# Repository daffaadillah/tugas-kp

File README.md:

# Penugasan Kerja Praktik PT. Infoglobal Teknologi Semesta

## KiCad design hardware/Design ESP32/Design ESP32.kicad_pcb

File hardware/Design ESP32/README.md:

# Design ESP32
Proyek Design ESP32 merupakan pembuatan ESP32 dari awal, mulai dari penentuan komponen pembentuk, perancangan komponen, hingga pembuatan design PCB. Tujuan proyek ini adalah membangun sistem ESP32 yang simpel sebagai media pembelajaran.
## Komponen Pembentuk
1. ESP32 S3 WROOM1
2. Regulator LDO 3,3V **AMS1117**
3. Kapasitor bypass (**10µF, 100nF**)  
4. Resistor (**R1, R2, R3, dan R4**)
5. UCB C Receptacle
6. Pin Header 01 × 08
7. S1 (**EN**) dan S2 (**BOOT**)
## Prinsip Kerja
### 1. Power manajemen
-  USB C, menyuplai tegangan 5V.  
-  AMS1117, menurunkan tegangan dari 5V ke 3V. Tegangan 3V yang kemudaian menyuplai ESP32 dan komponen pasif.
### 2. EN dan BOOT
-  EN, untuk mereset board.  
-  BOOT, untuk masuk ke mode pemrograman atau flash mode.
### 3. Resistor dan Kapasitor
-  Digunakan untuk filter tegangan, debouncing tombol, dan stabilisasi startup ESP32.
### 4. USB Data D+, D-
-  Memungkinkan penggunaan USB-TTL eksternal untuk pemrograman via TX/RX.
### 5. Header pin
-  Digunakan sebagai pin I/O eksternal. Bisa dijadikan input, output, PWM, SPI, I2C, UART, dll.

## Cuplikan Schematic

## Cuplikan LayOut PCB

## Cuplikan 3D View

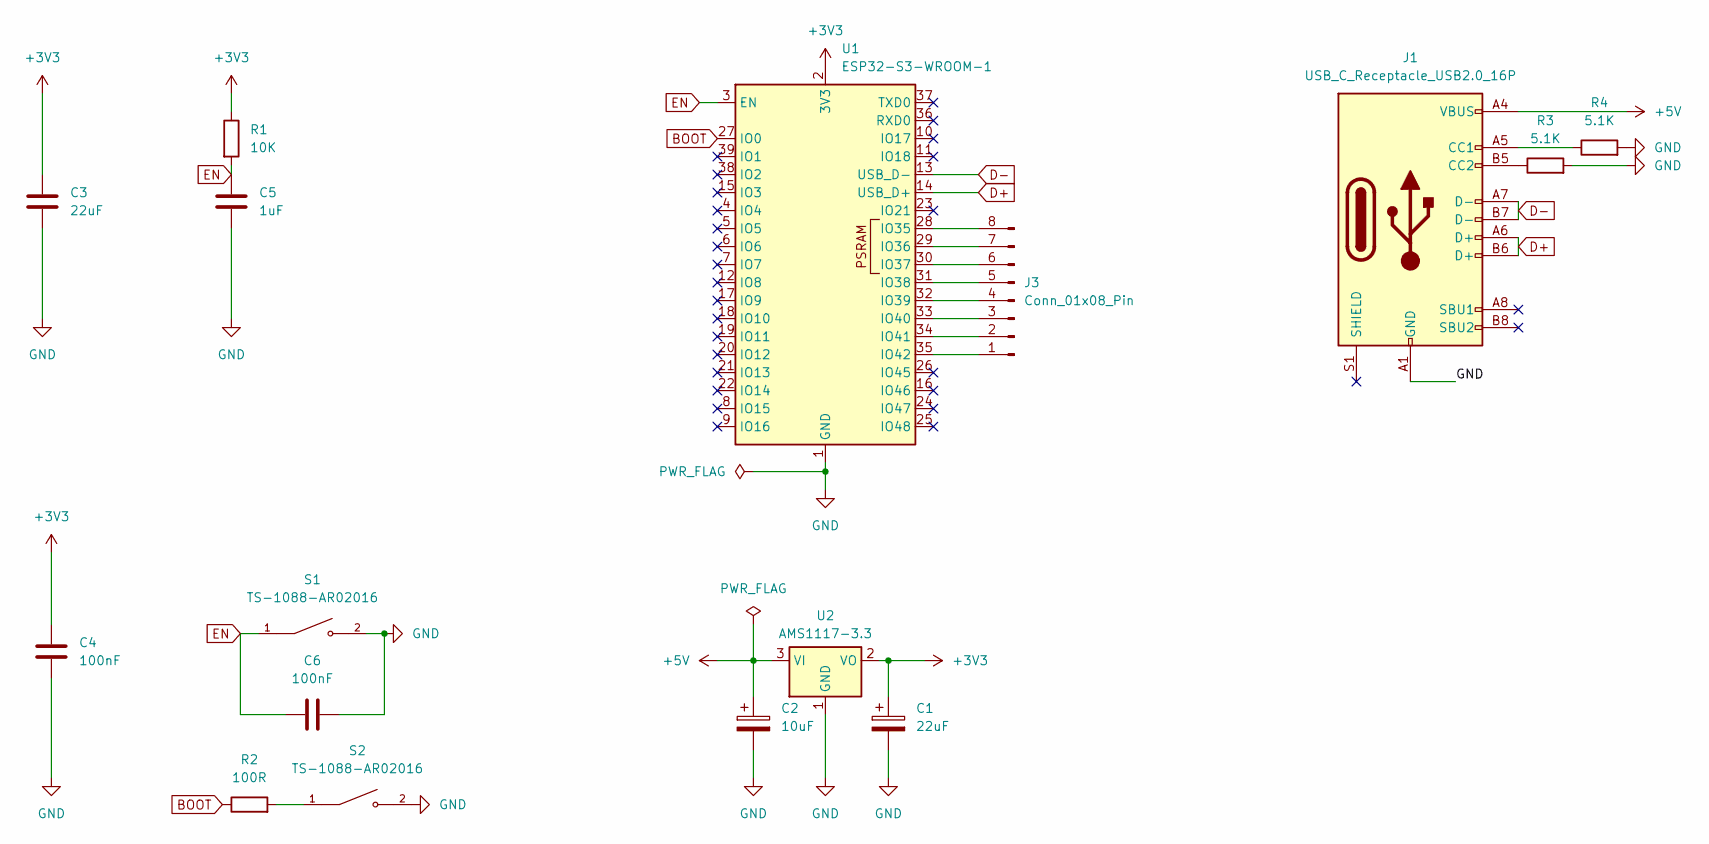
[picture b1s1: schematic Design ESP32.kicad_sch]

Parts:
C1: 22uF; CP_EIA-2012-15_AVX-P
C2: 10uF; CP_EIA-1608-10_AVX-L
C3: 22uF; C_0603_1608Metric
C4: 100nF; C_0603_1608Metric
C5: 1uF; R_0805_2012Metric
C6: 100nF; C_0805_2012Metric
J1: USB_C_Receptacle_USB2.0_16P; USB_C_Receptacle_GCT_USB4105-xx-A_16P_TopMnt_Horizontal
J3: Conn_01x08_Pin; PinHeader_1x08_P1.00mm_Vertical
R1: 10K; C_0805_2012Metric
R2: 100R; R_0805_2012Metric
R3, R4: 5.1K; R_0805_2012Metric
S1, S2: TS-1088-AR02016; SW_TS-1088-AR02016; PARTREV N/A
U1: ESP32-S3-WROOM-1
U2: AMS1117-3.3; SOT-223-3_TabPin2

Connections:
+3V3: C1.1, C3.1, C4.1, R1.1, U1.2 (3V3), U2.2 (VO)
+5V: C2.1, J1.A4 (VBUS), J1.A9 (VBUS), J1.B4 (VBUS), J1.B9 (VBUS), U2.3 (VI)
BOOT: R2.1, U1.27 (IO0)
D+: J1.A6 (D+), J1.B6 (D+), U1.14 (USB_D+)
D-: J1.A7 (D-), J1.B7 (D-), U1.13 (USB_D-)
EN: C5.1, C6.1, R1.2, S1.1, U1.3 (EN)
GND: C1.2, C2.2, C3.2, C4.2, C5.2, C6.2, J1.A1 (GND), J1.A12 (GND), J1.B1 (GND), J1.B12 (GND), R3.2, R4.2, S1.2, S2.2, U1.1 (GND), U1.40 (GND), U1.41 (GND), U2.1 (GND)
unnamed: J1.A5 (CC1), R4.1
unnamed: J1.B5 (CC2), R3.1
unnamed: J3.1, U1.35 (IO42)
unnamed: J3.2, U1.34 (IO41)
unnamed: J3.3, U1.33 (IO40)
unnamed: J3.4, U1.32 (IO39)
unnamed: J3.5, U1.31 (IO38)
unnamed: J3.6, U1.30 (IO37)
unnamed: J3.7, U1.29 (IO36)
unnamed: J3.8, U1.28 (IO35)
unnamed: R2.2, S2.1

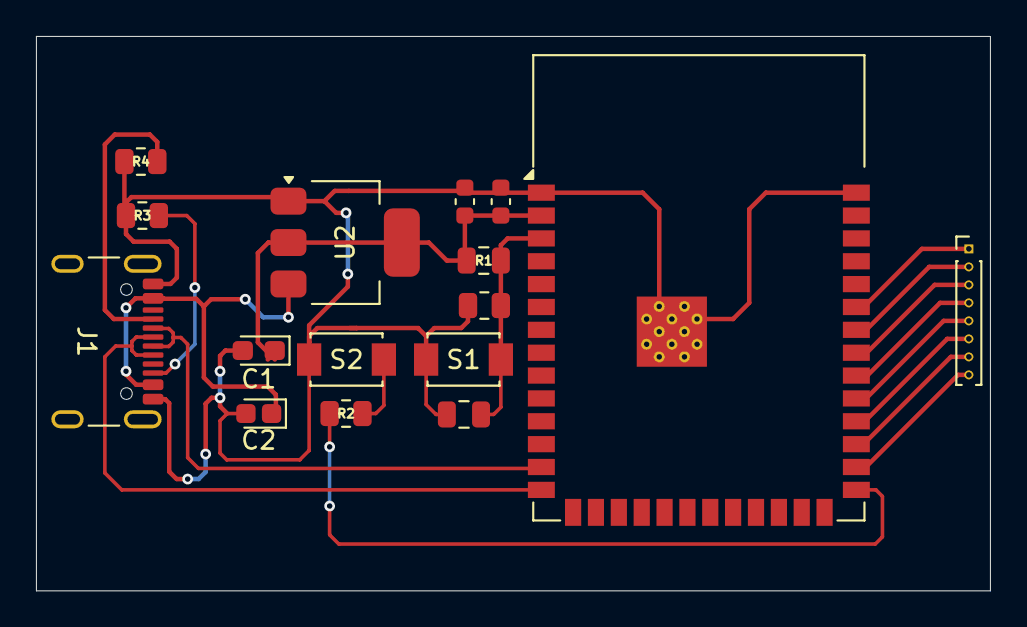
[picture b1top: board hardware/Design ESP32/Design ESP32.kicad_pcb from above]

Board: 2 copper layers, 53.0 x 30.8 mm, 16 parts (0 on the bottom side), 18 nets.

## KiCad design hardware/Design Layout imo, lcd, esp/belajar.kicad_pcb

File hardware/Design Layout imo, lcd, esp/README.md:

# ESP32 motion display module
Proyek ESP32 motion display module merupakan custom PCB untuk ESP32 yang diintegrasikan dengan sensor imo **MPU6050** dan LCD TFT **ILI9341**. Tujuannya yakni untuk dapat menampilkan nilai sudut kemiringan secara real-time dengan display.
## Komponen yang digunakan
-**ESP32 DEVKITV1**  : Mikrokontroler.  
-**MPU6050**         : Sensor accelerometer dan gyroscope 6-axis.  
-**ILI9341**         : Display.  
## Cuplikan Schematic

## kode Arduino IDE
```cpp  
#include <Wire.h>
#include <Adafruit_GFX.h>
#include <Adafruit_ILI9341.h>
#include <MPU6050.h>

// Pin konfigurasi untuk LCD TFT
#define TFT_CS     5
#define TFT_DC     2
#define TFT_RST    4

// Inisialisasi LCD TFT
Adafruit_ILI9341 tft = Adafruit_ILI9341(TFT_CS, TFT_DC, TFT_RST);

// Inisialisasi objek MPU6050
MPU6050 mpu;

void setup() {
  Serial.begin(115200);

  // Inisialisasi I2C MPU6050
  Wire.begin(21, 22); // SDA, SCL
  mpu.initialize();

  if (mpu.testConnection()) {
    Serial.println("MPU6050 connect");
  } else {
    Serial.println("Gagal connect ke MPU6050");
    while (1); // Berhenti
  }

  // Inisialisasi TFT
  tft.begin();
  tft.setRotation(1); // orientasi landscape
  tft.fillScreen(ILI9341_BLACK);
  tft.setTextSize(2);
  tft.setTextColor(ILI9341_WHITE);
}

void loop() {
  int16_t ax, ay, az;
  mpu.getAcceleration(&ax, &ay, &az);

  // menampilkan di serial monitor
  Serial.print("AX: "); Serial.print(ax);
  Serial.print(" AY: "); Serial.print(ay);
  Serial.print(" AZ: "); Serial.println(az);

  // membersihkan dan tampilkan di layar
  tft.fillScreen(ILI9341_BLACK);
  tft.setCursor(10, 20);
  tft.print("Accel X: "); tft.println(ax);

  tft.setCursor(10, 50);
  tft.print("Accel Y: "); tft.println(ay);

  tft.setCursor(10, 80);
  tft.print("Accel Z: "); tft.println(az);

  delay(500);
}
```
## Prinsip kerja
Prinsip kerja alat ini dimulai dari MPU6050 yang berfungsi sebagai sensor percepatan tiga sumbu (X, Y, Z). Sensor ini mendeteksi gerakan atau perubahan posisi, lalu mengirimkan data percepatan tersebut ke ESP32 melalui komunikasi I2C. ESP32 berperan sebagai pusat kontrol yang menerima, mengolah, dan menerjemahkan data percepatan dari sensor. Setelah data terbaca dan diproses, ESP32 mengirimkan hasilnya ke layar TFT LCD melalui komunikasi SPI. Tampilan pada layar diperbarui secara berkala untuk menunjukkan nilai percepatan terbaru dari ketiga sumbu. Dengan demikian, alat tersebut dapat digunakan untuk memantau gerakan atau orientasi secara real-time, yang divisualisasikan langsung melalui display yang mewakili nilai percepatan sumbu X, Y, dan Z.
## Cuplikan hasil custom PCB

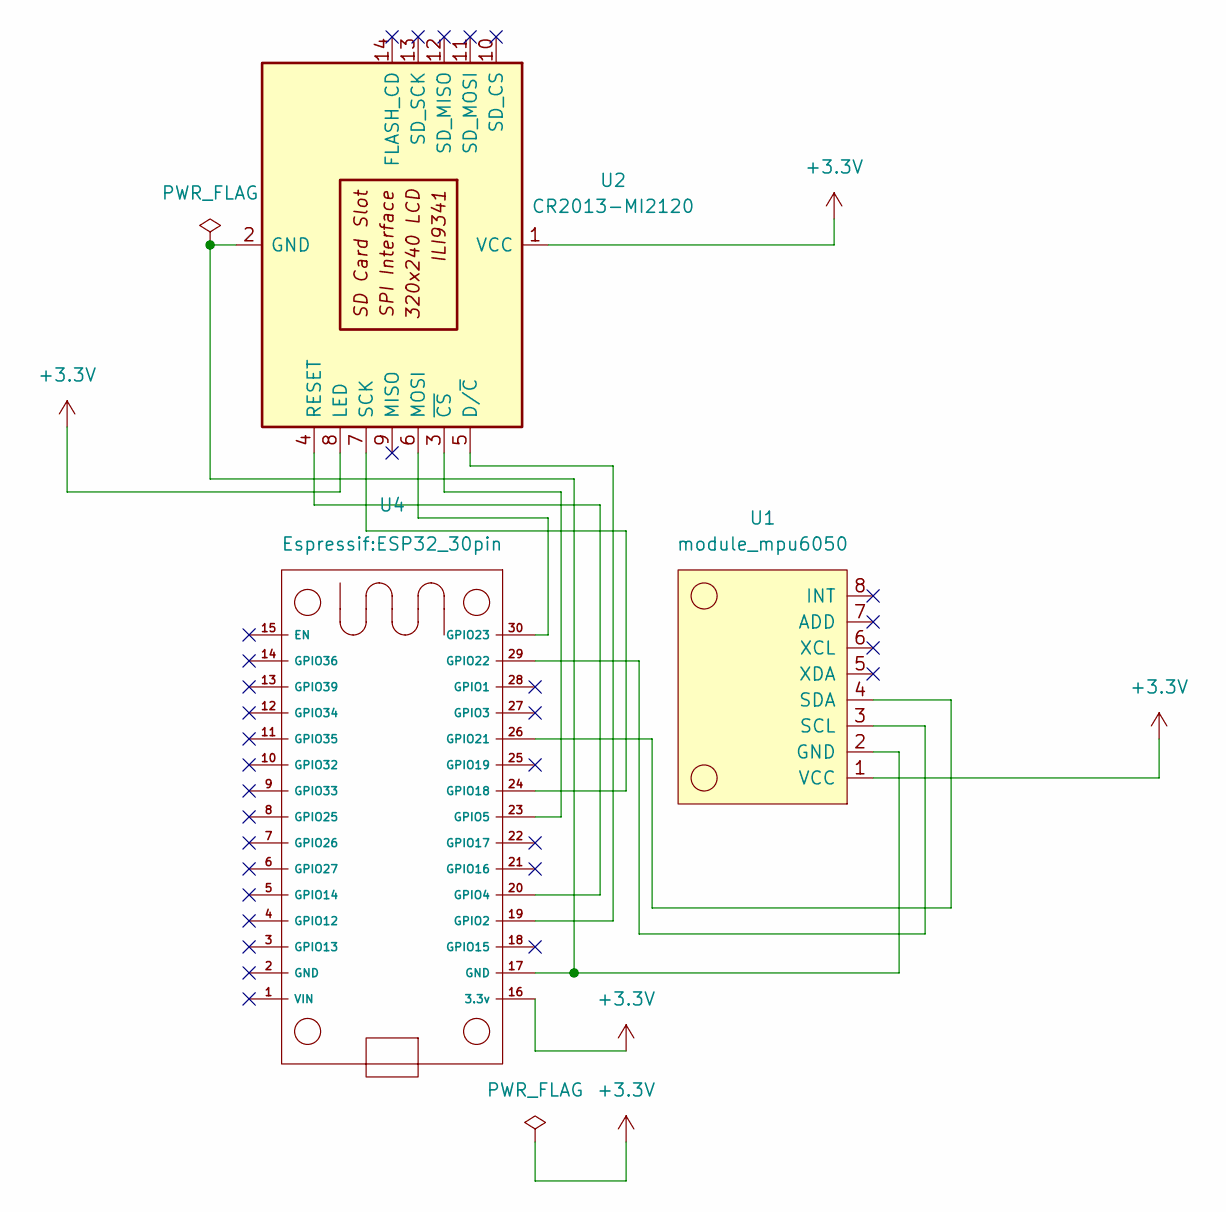
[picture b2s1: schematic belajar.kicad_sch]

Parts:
U1: module_mpu6050
U2: CR2013-MI2120
U4: ESP32_30pin

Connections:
+3.3V: U1.1 (VCC), U2.1 (VCC), U2.8 (LED), U4.16 (3.3v)
unnamed: U1.2 (GND), U2.2 (GND), U4.17 (GND)
unnamed: U1.3 (SCL), U4.29 (GPIO22)
unnamed: U1.4 (SDA), U4.26 (GPIO21)
unnamed: U2.5 (D/~C), U4.19 (GPIO2)
unnamed: U2.6 (MOSI), U4.30 (GPIO23)
unnamed: U2.4 (RESET), U4.20 (GPIO4)
unnamed: U2.7 (SCK), U4.24 (GPIO18)
unnamed: U2.3 (~CS), U4.23 (GPIO5)

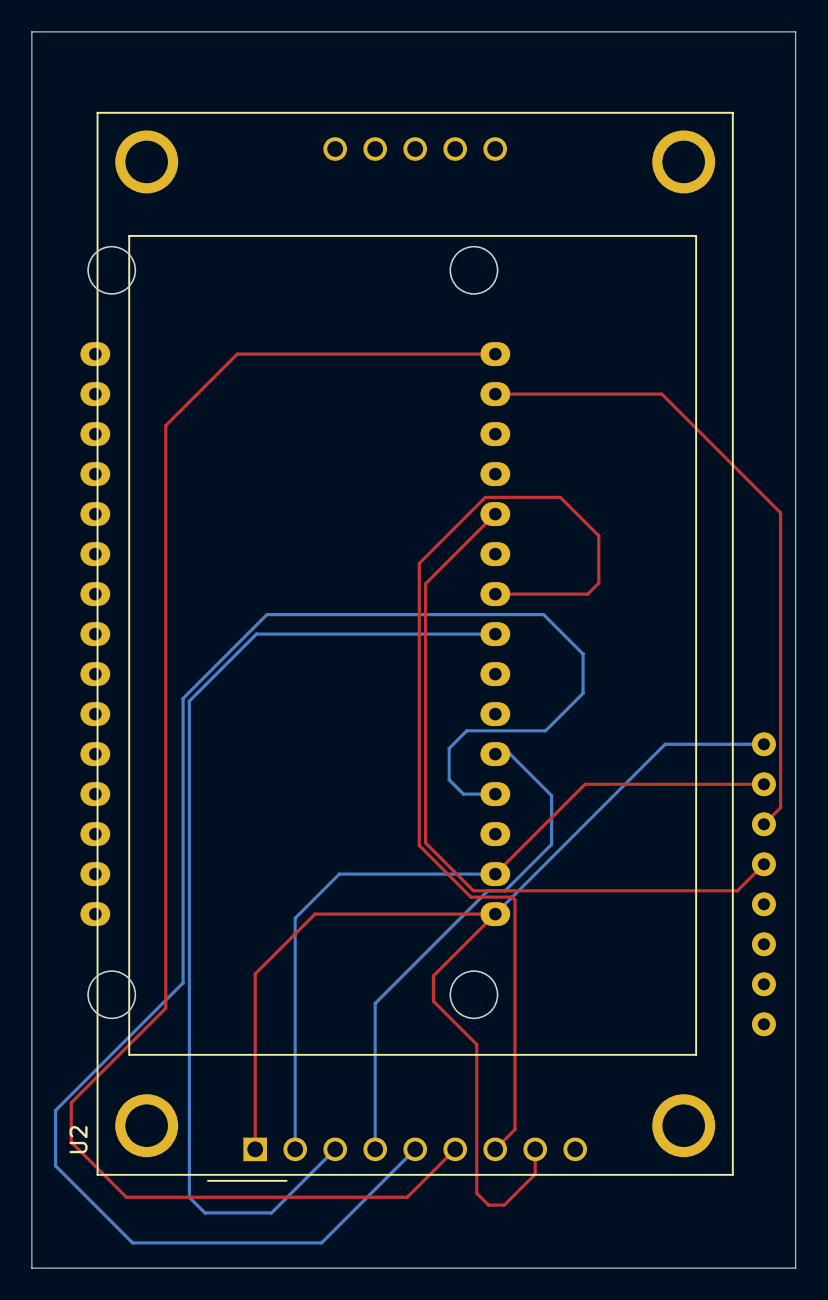
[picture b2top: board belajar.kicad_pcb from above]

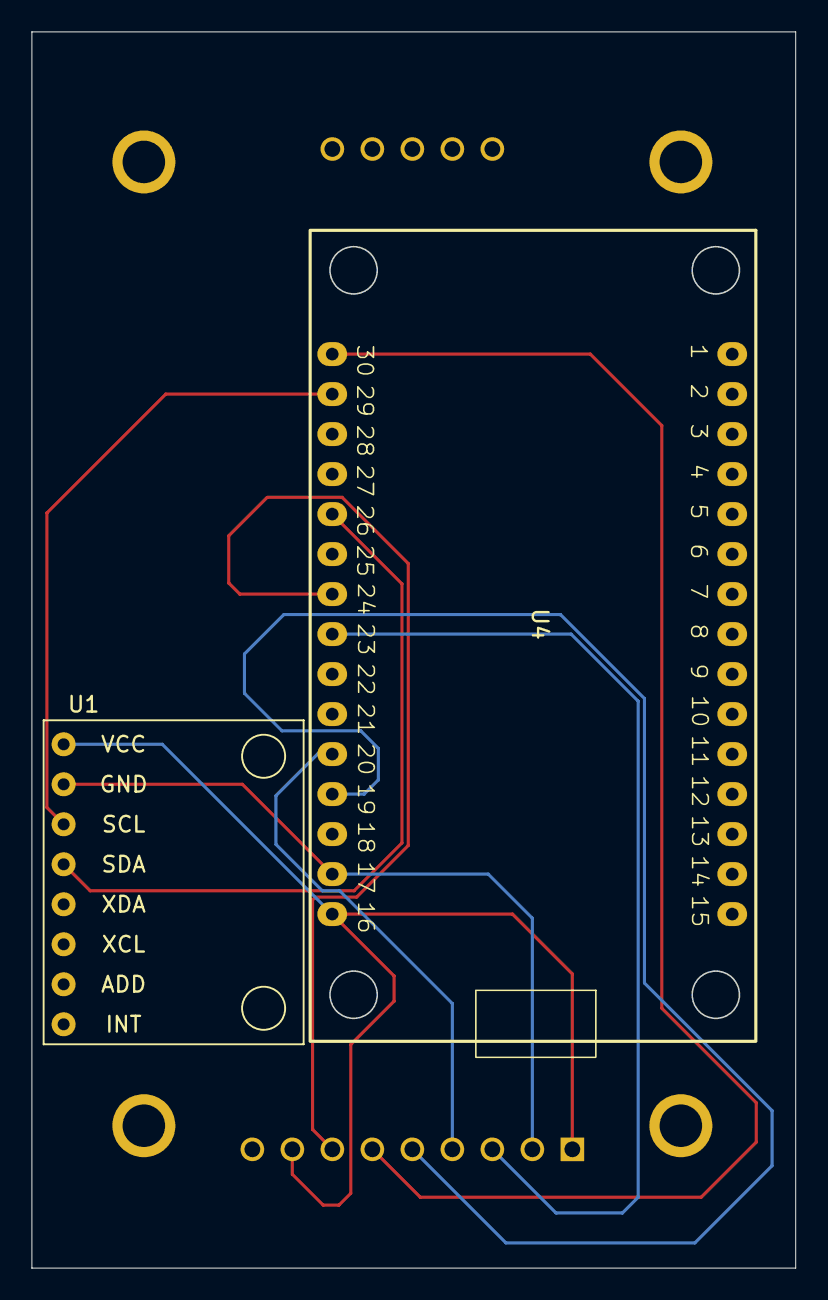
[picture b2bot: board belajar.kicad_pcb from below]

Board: 2 copper layers, 48.5 x 78.5 mm, 3 parts (2 on the bottom side), 9 nets.

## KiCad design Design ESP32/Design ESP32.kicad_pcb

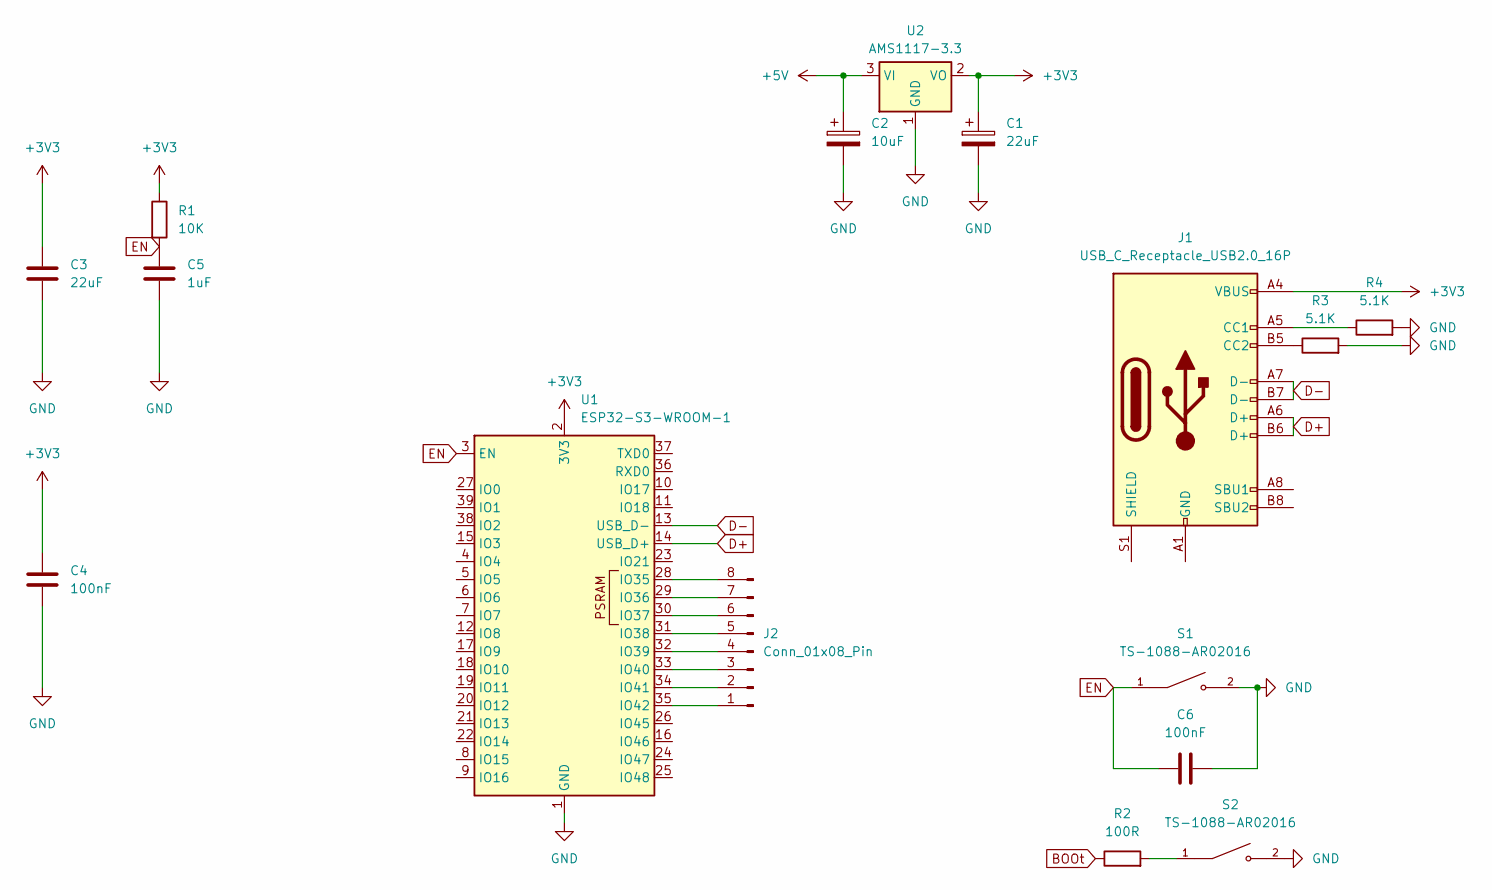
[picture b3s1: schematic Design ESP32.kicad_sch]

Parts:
C1, C3: 22uF; C_0805_2012Metric
C2: 10uF; C_0805_2012Metric
C4, C6: 100nF; C_0805_2012Metric
C5: 1uF; R_0805_2012Metric
J1: USB_C_Receptacle_USB2.0_16P; USB_C_Receptacle_GCT_USB4105-xx-A_16P_TopMnt_Horizontal
J2: Conn_01x08_Pin; PinHeader_1x08_P1.00mm_Vertical
R1: 10K; C_0805_2012Metric
R2: 100R; R_0805_2012Metric
R3, R4: 5.1K; R_0805_2012Metric
S1, S2: TS-1088-AR02016; SW_TS-1088-AR02016; PARTREV N/A
U1: ESP32-S3-WROOM-1
U2: AMS1117-3.3; SOT-223-3_TabPin2

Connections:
+3V3: C1.1, C3.1, C4.1, J1.A4 (VBUS), J1.A9 (VBUS), J1.B4 (VBUS), J1.B9 (VBUS), R1.1, U1.2 (3V3), U2.2 (VO)
+5V: C2.1, U2.3 (VI)
BOOt: R2.1
D+: J1.A6 (D+), J1.B6 (D+), U1.14 (USB_D+)
D-: J1.A7 (D-), J1.B7 (D-), U1.13 (USB_D-)
EN: C5.1, C6.1, R1.2, S1.1, U1.3 (EN)
GND: C1.2, C2.2, C3.2, C4.2, C5.2, C6.2, R3.2, R4.2, S1.2, S2.2, U1.1 (GND), U1.40 (GND), U1.41 (GND), U2.1 (GND)
unnamed: J1.A5 (CC1), R4.1
unnamed: J1.B5 (CC2), R3.1
unnamed: J1.A1 (GND), J1.A12 (GND), J1.B1 (GND), J1.B12 (GND)
unnamed: J2.1, U1.35 (IO42)
unnamed: J2.2, U1.34 (IO41)
unnamed: J2.3, U1.33 (IO40)
unnamed: J2.4, U1.32 (IO39)
unnamed: J2.5, U1.31 (IO38)
unnamed: J2.6, U1.30 (IO37)
unnamed: J2.7, U1.29 (IO36)
unnamed: J2.8, U1.28 (IO35)
unnamed: R2.2, S2.1

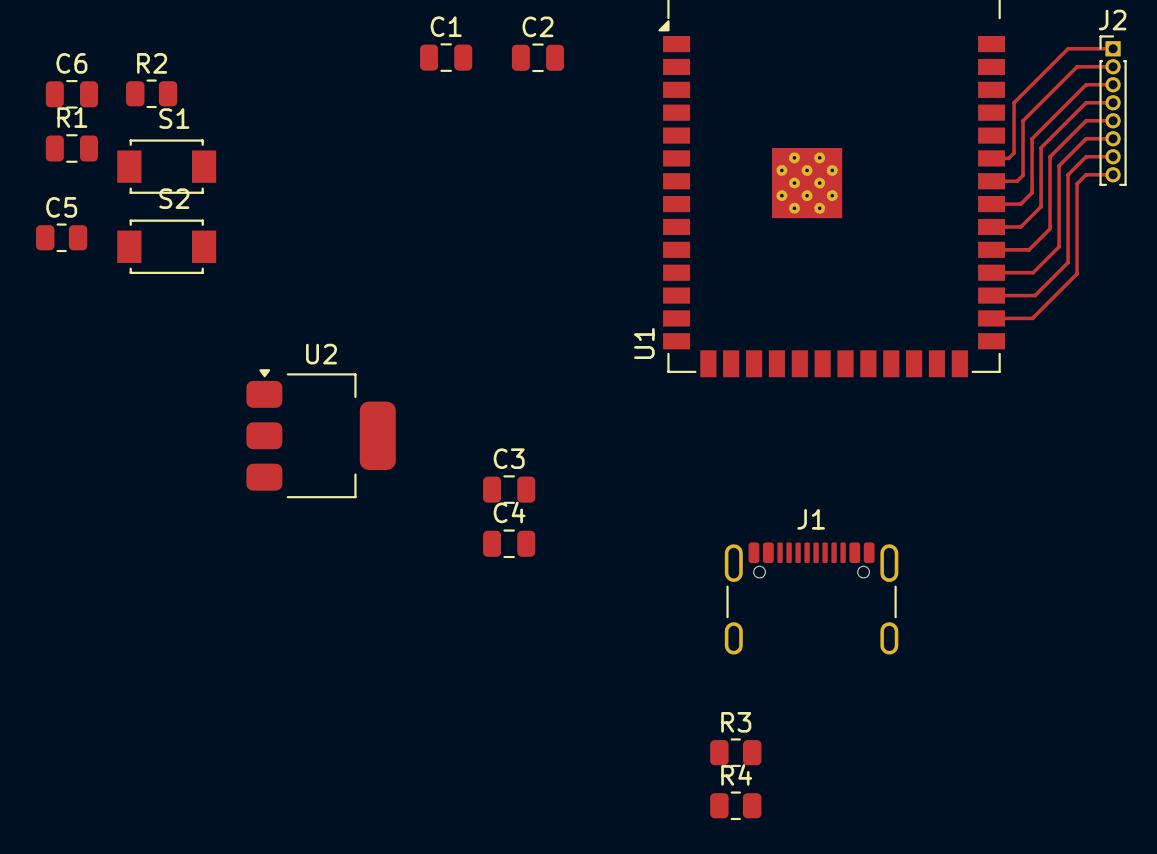
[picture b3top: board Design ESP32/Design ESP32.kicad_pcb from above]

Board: 2 copper layers, 16 parts (0 on the bottom side), 18 nets.

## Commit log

2025-07-04 add ESP32 board design
2025-07-04 edit skematik
2025-07-04 test
2025-07-04 test tugas awal
2025-07-07 crosscheck schenmatic, progres track pcb
2025-07-07 jalur pcb, penanganan error 36 to 11
2025-07-08 lanjut penanganan error dan penyelesaian design ESP32
2025-07-08 update footprint C1, C2
2025-07-09 folder images
2025-07-18 upload code
2025-07-24 upload kode
